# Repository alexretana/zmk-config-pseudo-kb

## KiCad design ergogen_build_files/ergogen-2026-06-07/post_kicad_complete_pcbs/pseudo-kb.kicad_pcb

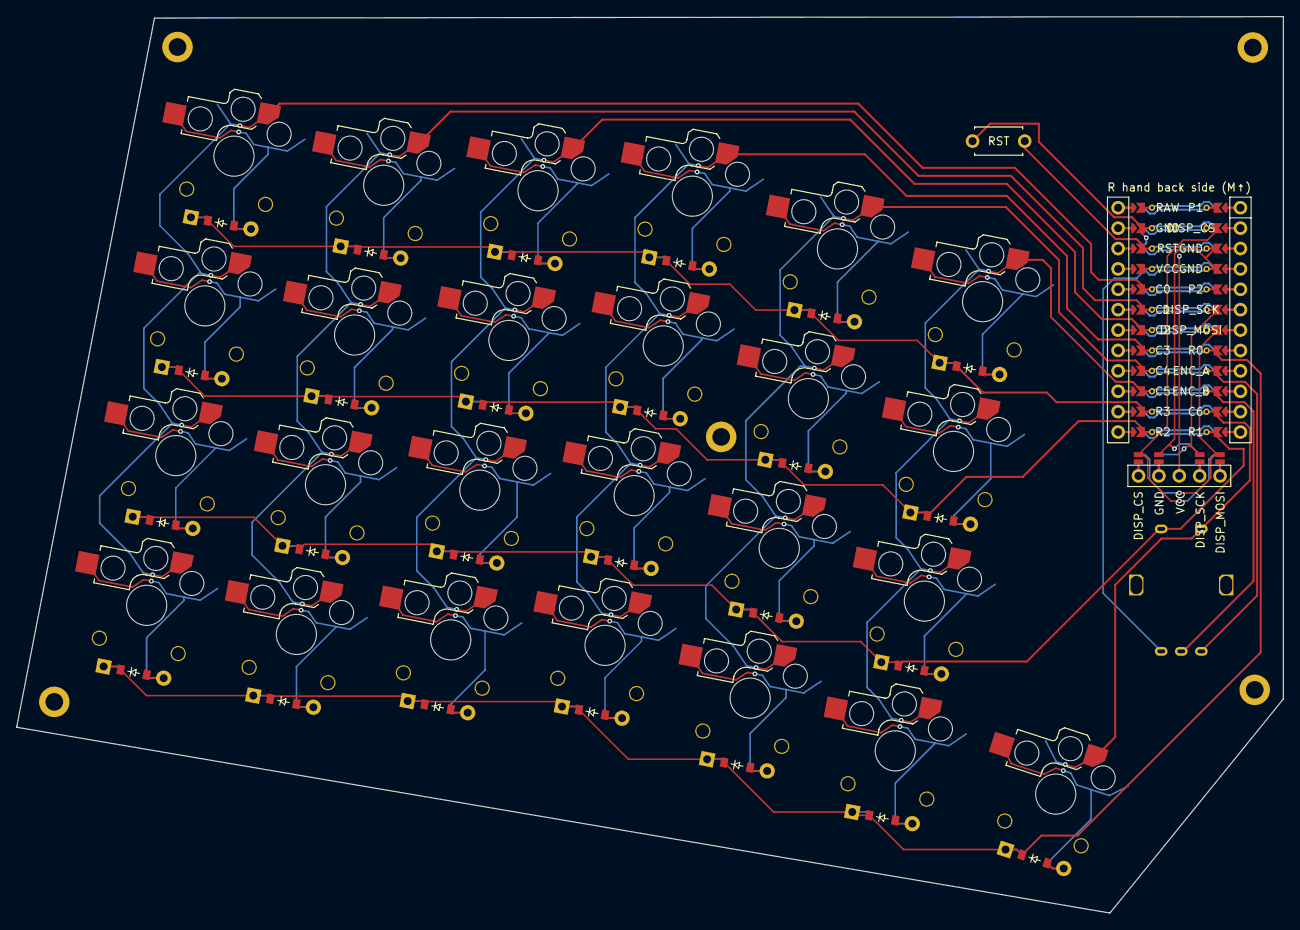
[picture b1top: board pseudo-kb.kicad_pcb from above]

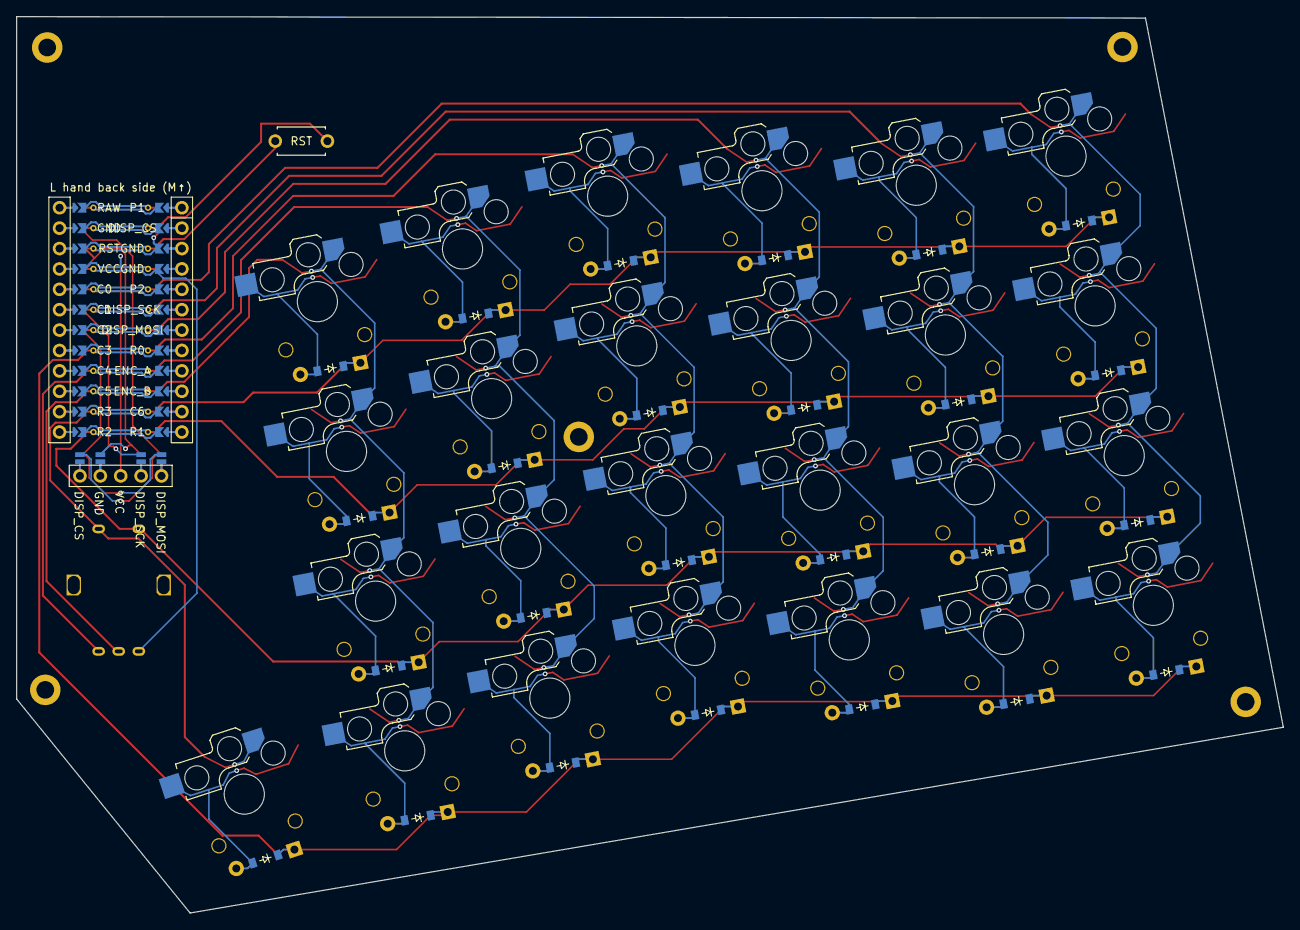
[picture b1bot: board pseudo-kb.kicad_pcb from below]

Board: 2 copper layers, 157.8 x 111.7 mm, 59 parts (25 on the bottom side), 48 nets.

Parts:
D1, D2, D3, D4, D5, D6, D7, D8, D9, D10, D11, D12, D13, D14, D15, D16, D17, D18, D19, D20, D21, D22, D23, D24, D25: diode_tht_sod123
DISP1: display_nice_view
H1, H2, H3, H4, H5: mounting_hole_plated
MCU1: mcu_nice_nano
RE1: rotary_encoder_ec11_ec12
RST1: reset_switch_tht_top
S1, S2, S3, S4, S5, S6, S7, S8, S9, S10, S11, S12, S13, S14, S15, S16, S17, S18, S19, S20, S21, S22, S23, S24, S25: switch_choc_v1_v2

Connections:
C0: MCU1.120, S1.1, S2.1, S3.1, S4.1
C1: MCU1.119, S5.1, S6.1, S7.1, S8.1
C2: MCU1.118, S9.1, S10.1, S11.1, S12.1
C3: MCU1.117, S13.1, S14.1, S15.1, S16.1
C4: MCU1.116, S17.1, S18.1, S19.1, S20.1
C5: MCU1.115, S21.1, S22.1, S23.1, S24.1
C6: MCU1.111, RE1.S2, S25.1
DISP1_1: DISP1.1, DISP1.10, DISP1.23
DISP1_2: DISP1.2, DISP1.11, DISP1.22
DISP1_4: DISP1.4, DISP1.12, DISP1.21
DISP1_5: DISP1.5, DISP1.13, DISP1.20
DISP_CS: DISP1.14, DISP1.24, MCU1.102
DISP_MOSI: DISP1.17, DISP1.27, MCU1.107
DISP_SCK: DISP1.16, DISP1.26, MCU1.106
ENC_A: MCU1.109, RE1.A
ENC_B: MCU1.110, RE1.B
GND: DISP1.15, DISP1.25, MCU1.103, MCU1.104, MCU1.123, RE1.C, RST1.2
R0: D1.1, D5.1, D9.1, D13.1, D17.1, D24.1, D25.1, MCU1.108
R1: D2.1, D6.1, D10.1, D14.1, D18.1, D21.1, MCU1.112, RE1.S1
R2: D3.1, D7.1, D11.1, D15.1, D19.1, D22.1, MCU1.113
R3: D4.1, D8.1, D12.1, D16.1, D20.1, D23.1, MCU1.114
RST: MCU1.122, RST1.1
VCC: DISP1.3, MCU1.121
far_lower: D25.2, S25.2
home_lower: D24.2, S24.2
index_bottom: D18.2, S18.2
index_home: D19.2, S19.2
index_top: D20.2, S20.2
index_utils: D17.2, S17.2
inner_bottom: D21.2, S21.2
inner_home: D22.2, S22.2
inner_top: D23.2, S23.2
middle_bottom: D14.2, S14.2
middle_home: D15.2, S15.2
middle_top: D16.2, S16.2
middle_utils: D13.2, S13.2
outer_bottom: D2.2, S2.2
outer_home: D3.2, S3.2
outer_top: D4.2, S4.2
outer_utils: D1.2, S1.2
pinky_bottom: D6.2, S6.2
pinky_home: D7.2, S7.2
pinky_top: D8.2, S8.2
pinky_utils: D5.2, S5.2
ring_bottom: D10.2, S10.2
ring_home: D11.2, S11.2
ring_top: D12.2, S12.2
ring_utils: D9.2, S9.2

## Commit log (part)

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2026-06-07 Bring in full zmk definiton for pseudo-kb and ergogen generated files + kicad completed files
2026-06-07 Fix minor mistakes after referencing ergogen files
2026-06-07 Make fixes to issues in CI/CD
2026-06-09 dongle needs config to allow it to work as usb host
2026-06-23 debug: strip nice!view from half builds to isolate boot crash
2026-06-23 dongle: explicitly set ZMK_SPLIT_ROLE_CENTRAL=y in conf
2026-06-23 dongle: explicitly enable BT_CENTRAL at Zephyr level
2026-06-23 dongle: move all split BLE central config explicitly into conf file
